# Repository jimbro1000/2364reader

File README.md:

# 2364 Masked Rom Adapter for EPROM programmer

You can't re-program a masked rom but you can still
read it. This adapts the pin positions of old 2364
masked roms to use the same pin positions as a 27C64
so that a regular EPROM programmer can easily read
the contents of the masked ROM.

The 2364 and pin compatible masked roms were common in
the 80s era of 8-bit home computers (Commodore VIC-20,
Commodore 64, Tandy CoCos, etc). Before attempting to
use this adapter make sure that the rom **is** pin
compatible. If incompatible, at best you will create
a corrupted ROM image, at worst you could damage the
ROM. Most programmers will protect themselves from
damage but do not assume this is the case.

## Why do you need it?

While masked roms are generally robust they do fail,
this adapter provides a simple way to read the rom
image using an eprom programmer. In practical terms
this is a way to verify a real rom against a known
rom image. Or maybe to generate a new rom image where
one doesn't exist.

Some modern recreations of old 8-bit computers have
opted to use 27/28C64s instead of the original masked
roms in the name of avoiding unobtainable parts. This
adapter can also be used to fit original roms. If a
larger capacity eprom is used (eg. 27C256) this 
adapater will not really help.

## BOM

| Position | Component                                | Quantity |
|:---------|:-----------------------------------------|:--------:|
| U1       | 24 pin dip socket 15mm wide              | 1        |
| U2       | 1x14 pin 2.54mm pitch male header        | 2        |
| JP1      | 1x3 pin 2.54mm pitch male header         | 1        |
| JP1      | 2.54mm jumper                            | 1        |

note: it is highly recommended to use round (turned) pin headers for
U2 instead of the bulkier square pin versions as these are kinder to
sockets

## Assembly

1. Fit two rows of pins to the bottom of the board in
the longer rows (14 pins each)

2. Trim the pin ends on the top of the board to allow
clean fitting of a socket

3. Fit a 24 pin socket on the top of the board

4. Fit a row of 3 pins to the board at JP1

5. Use a jumper on JP1 on the 8k side

## Usage

1. Move the jumper to the 8k side of JP1

2. Fit your 2364 masked rom in the socket

3. Place the board and rom in your eprom reader/programmer

4. Set the programmer to use a 27C64

5. Read the rom as normal

### Reading a 2332 rom (4K bytes/32K bits)

While I intended the jumper to gracefully handle A12
addressing when reading a 2332 but in the current
design it gives unexpected results. Until fixed the
steps for reading a 2332 are the same as for the 8K 2364. 
The end result is that the upper 4K are read as $FF
instead of repeating the image.

A change to the board has been made to circumvent the 
problem but is not tested.

#### Ignore until fixed:

1. Move the jumper to the 4k side of the board

2. Fit your 2332 masked rom in the socket

3. Proceed as normal for a 2364 from step 3

Note: The image read from the rom will show as an 8k image, 
but the image repeats after the first 4k. Trim the image at
the 4k mark to convert the result into the correct 4k size.

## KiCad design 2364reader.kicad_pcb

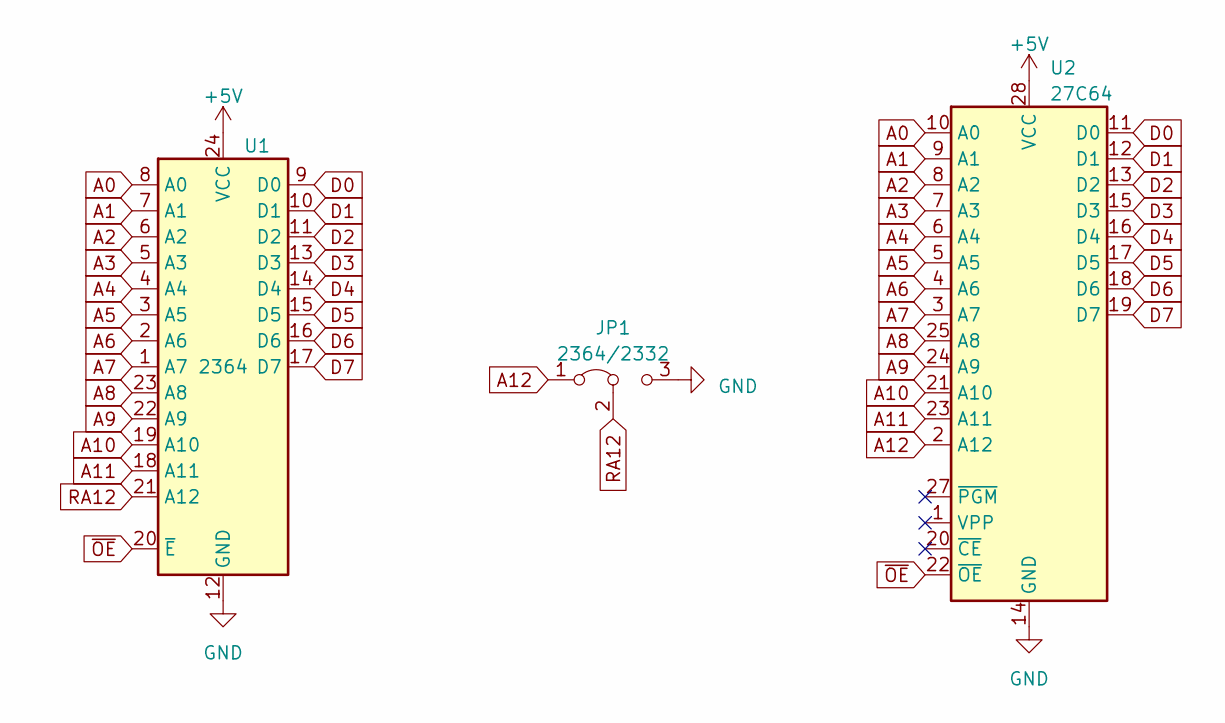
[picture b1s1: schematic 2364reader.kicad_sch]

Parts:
JP1: 2364/2332; PinHeader_1x03_P2.54mm_Horizontal
U1: 2364; DIP-24_W15.24mm
U2: 27C64; DIP-28_W15.24mm_Socket

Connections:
+5V: U1.24 (VCC), U2.28 (VCC)
A0: U1.8 (A0), U2.10 (A0)
A1: U1.7 (A1), U2.9 (A1)
A2: U1.6 (A2), U2.8 (A2)
A3: U1.5 (A3), U2.7 (A3)
A4: U1.4 (A4), U2.6 (A4)
A5: U1.3 (A5), U2.5 (A5)
A6: U1.2 (A6), U2.4 (A6)
A7: U1.1 (A7), U2.3 (A7)
A8: U1.23 (A8), U2.25 (A8)
A9: U1.22 (A9), U2.24 (A9)
A10: U1.19 (A10), U2.21 (A10)
A11: U1.18 (A11), U2.23 (A11)
A12: JP1.1 (A), U2.2 (A12)
D0: U1.9 (D0), U2.11 (D0)
D1: U1.10 (D1), U2.12 (D1)
D2: U1.11 (D2), U2.13 (D2)
D3: U1.13 (D3), U2.15 (D3)
D4: U1.14 (D4), U2.16 (D4)
D5: U1.15 (D5), U2.17 (D5)
D6: U1.16 (D6), U2.18 (D6)
D7: U1.17 (D7), U2.19 (D7)
GND: JP1.3 (B), U1.12 (GND), U2.14 (GND)
RA12: JP1.2 (C), U1.21 (A12)
~OE: U1.20 (~E), U2.22 (~OE)

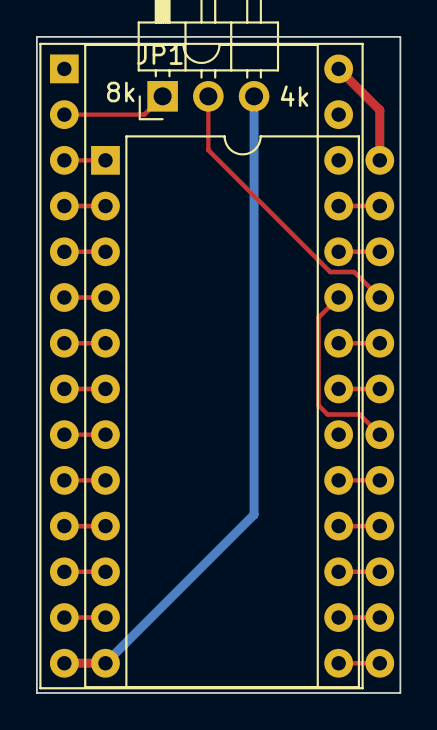
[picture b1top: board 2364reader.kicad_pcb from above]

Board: 2 copper layers, 20.2 x 36.4 mm, 3 parts (0 on the bottom side), 25 nets.

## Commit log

2023-03-29 adapt to accept 2332
2023-03-30 tidy up readme
2023-04-13 revise board to fix 2332 problem
2023-04-13 add license
